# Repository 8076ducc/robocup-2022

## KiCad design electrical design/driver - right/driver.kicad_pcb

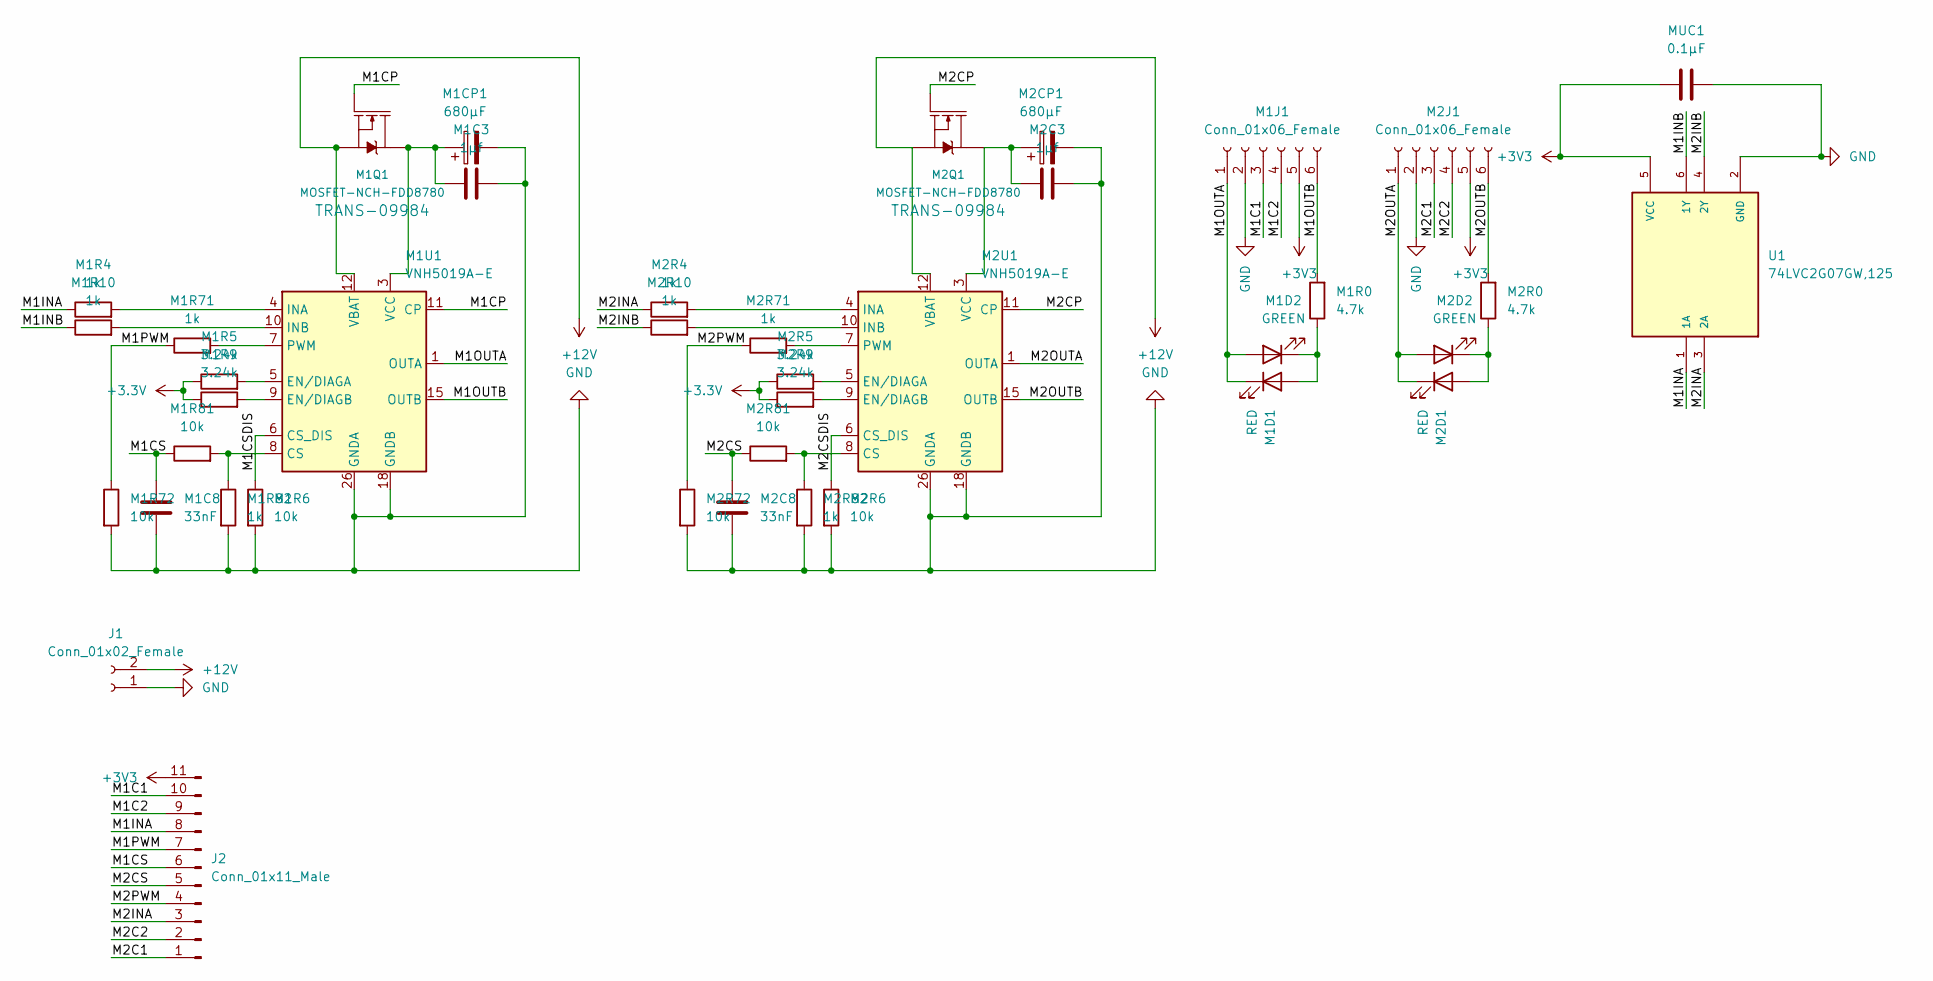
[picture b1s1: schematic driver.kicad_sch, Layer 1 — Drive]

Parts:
J1: Conn_01x02_Female; AMASS_XT30U-F_1x02_P5.0mm_Vertical
J2: Conn_01x11_Male; PinHeader_1x11_P2.54mm_Vertical
M1C3, M2C3: 1µf; C_0603_1608Metric
M1C8, M2C8: 33nF; C_0603_1608Metric
M1CP1, M2CP1: 680µF; CP_Radial_D8.0mm_P3.50mm
M1D1, M2D1: RED; LED-0603
M1D2, M2D2: GREEN; LED-0603
M1J1, M2J1: Conn_01x06_Female; JST_PH_B6B-PH-SM4-TB_1x06-1MP_P2.00mm_Vertical
M1Q1, M2Q1: MOSFET-NCH-FDD8780; DPAK
M1R0, M2R0: 4.7k; R_0603_1608Metric
M1R4, M1R10, M1R71, M1R82, M2R4, M2R10, M2R71, M2R82: 1k; R_0603_1608Metric
M1R5, M1R9, M2R5, M2R9: 3.24k; R_0603_1608Metric
M1R6, M1R72, M1R81, M2R6, M2R72, M2R81: 10k; R_0603_1608Metric
M1U1, M2U1: VNH5019A-E; ST_MultiPowerSO-30
MUC1: 0.1µF; C_0603_1608Metric
U1: 74LVC2G07GW,125; SOP65P210X110-6N

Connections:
+12V: J1.2, M1Q1.3 (S), M1U1.12 (VBAT), M2Q1.3 (S), M2U1.12 (VBAT)
/M1C1: J2.10, M1J1.3
/M1C2: J2.9, M1J1.4
/M1CP: M1Q1.1 (G), M1U1.11 (CP)
/M1CS: J2.6, M1C8.1, M1R81.1
/M1CSDIS: M1R6.1, M1U1.6 (CS_DIS)
/M1INA: J2.8, M1R4.1, U1.1 (1A)
/M1INB: M1R10.1, U1.6 (1Y)
/M1OUTA: M1D1.1 (K), M1D2.2 (A), M1J1.1, M1J1.MP, M1U1.1 (OUTA), M1U1.25 (OUTA), M1U1.30 (OUTA), M1U1.33 (OUTA)
/M1OUTB: M1J1.6, M1J1.MP, M1R0.2, M1U1.15 (OUTB), M1U1.16 (OUTB), M1U1.21 (OUTB), M1U1.32 (OUTB)
/M1PWM: J2.7, M1R71.1, M1R72.1
/M2C1: J2.1, M2J1.3
/M2C2: J2.2, M2J1.4
/M2CP: M2Q1.1 (G), M2U1.11 (CP)
/M2CS: J2.5, M2C8.1, M2R81.1
/M2CSDIS: M2R6.1, M2U1.6 (CS_DIS)
/M2INA: J2.3, M2R4.1, U1.3 (2A)
/M2INB: M2R10.1, U1.4 (2Y)
/M2OUTA: M2D1.1 (K), M2D2.2 (A), M2J1.1, M2U1.1 (OUTA), M2U1.25 (OUTA), M2U1.30 (OUTA), M2U1.33 (OUTA)
/M2OUTB: M2J1.6, M2R0.2, M2U1.15 (OUTB), M2U1.16 (OUTB), M2U1.21 (OUTB), M2U1.32 (OUTB)
/M2PWM: J2.4, M2R71.1, M2R72.1
GND: J1.1, M1C3.2, M1C8.2, M1CP1.2, M1J1.2, M1R6.2, M1R72.2, M1R82.2, M1U1.18 (GNDB), M1U1.19 (GNDB), M1U1.20 (GNDB), M1U1.26 (GNDA), M1U1.27 (GNDA), M1U1.28 (GNDA), M2C3.2, M2C8.2, M2CP1.2, M2J1.2, M2R6.2, M2R72.2, M2R82.2, M2U1.18 (GNDB), M2U1.19 (GNDB), M2U1.20 (GNDB), M2U1.26 (GNDA), M2U1.27 (GNDA), M2U1.28 (GNDA), MUC1.1, U1.2 (GND)
unnamed: M1C3.1, M1CP1.1, M1Q1.4 (D), M1U1.3 (VCC), M1U1.13 (VCC), M1U1.23 (VCC), M1U1.31 (VCC)
unnamed: M1D1.2 (A), M1D2.1 (K), M1R0.1
unnamed: M1R4.2, M1U1.4 (INA)
unnamed: M1R5.2, M1U1.5 (EN/DIAGA)
unnamed: M1R9.2, M1U1.9 (EN/DIAGB)
unnamed: M1R10.2, M1U1.10 (INB)
unnamed: M1R71.2, M1U1.7 (PWM)
unnamed: M1R81.2, M1R82.1, M1U1.8 (CS)
unnamed: M2C3.1, M2CP1.1, M2Q1.4 (D), M2U1.3 (VCC), M2U1.13 (VCC), M2U1.23 (VCC), M2U1.31 (VCC)
unnamed: M2D1.2 (A), M2D2.1 (K), M2R0.1
unnamed: M2R4.2, M2U1.4 (INA)
unnamed: M2R5.2, M2U1.5 (EN/DIAGA)
unnamed: M2R9.2, M2U1.9 (EN/DIAGB)
unnamed: M2R10.2, M2U1.10 (INB)
unnamed: M2R71.2, M2U1.7 (PWM)
unnamed: M2R81.2, M2R82.1, M2U1.8 (CS)

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
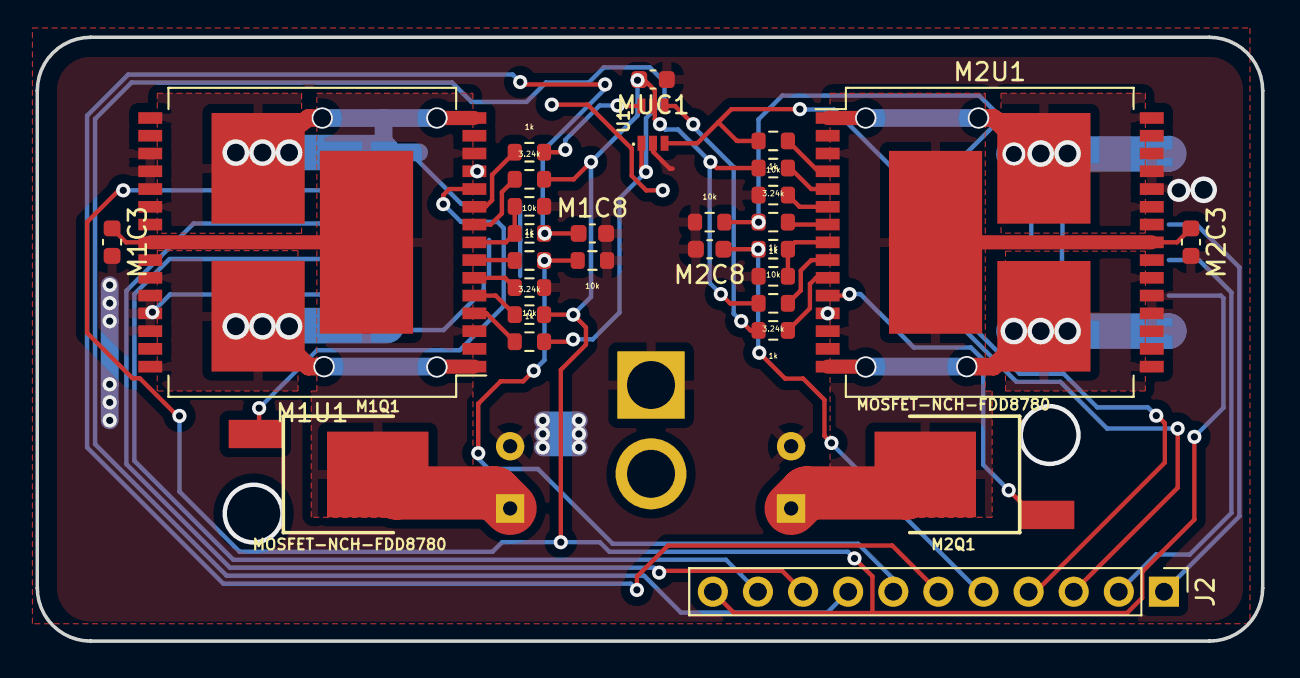
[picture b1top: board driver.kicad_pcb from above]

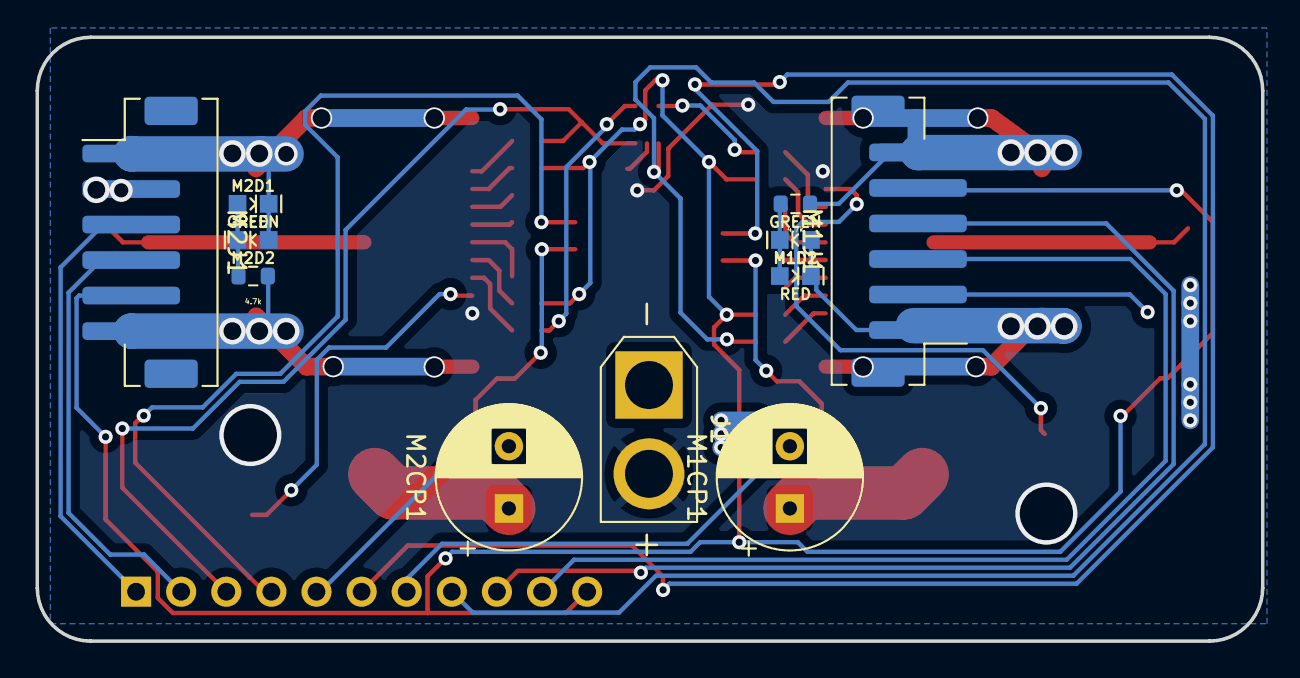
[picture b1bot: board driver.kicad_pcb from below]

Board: 2 copper layers, 69.0 x 34.0 mm, 40 parts (11 on the bottom side), 39 nets.

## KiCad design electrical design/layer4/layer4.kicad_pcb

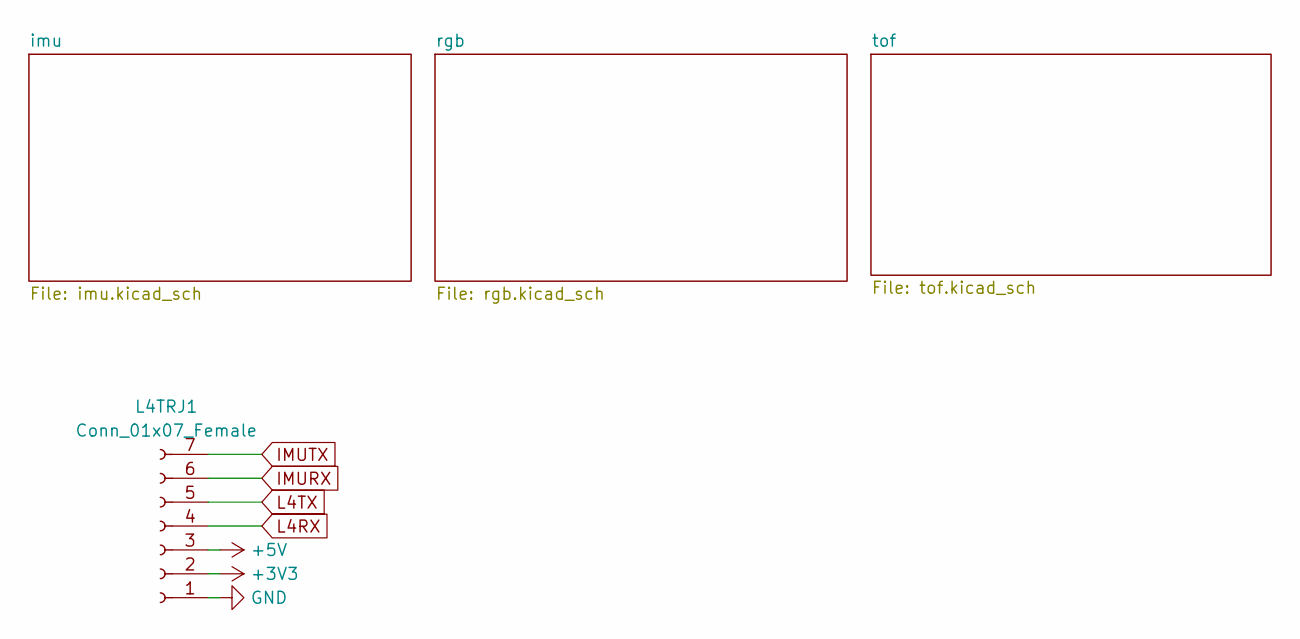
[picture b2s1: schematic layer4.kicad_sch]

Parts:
L4TRJ1: Conn_01x07_Female; JST_SH_BM07B-SRSS-TB_1x07-1MP_P1.00mm_Vertical

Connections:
+3V3: L4TRJ1.2; also elsewhere on the board
+5V: L4TRJ1.3; also elsewhere on the board
GND: L4TRJ1.1; also elsewhere on the board
IMURX: L4TRJ1.6; also elsewhere on the board
IMUTX: L4TRJ1.7; also elsewhere on the board
L4RX: L4TRJ1.4; also elsewhere on the board
L4TX: L4TRJ1.5; also elsewhere on the board

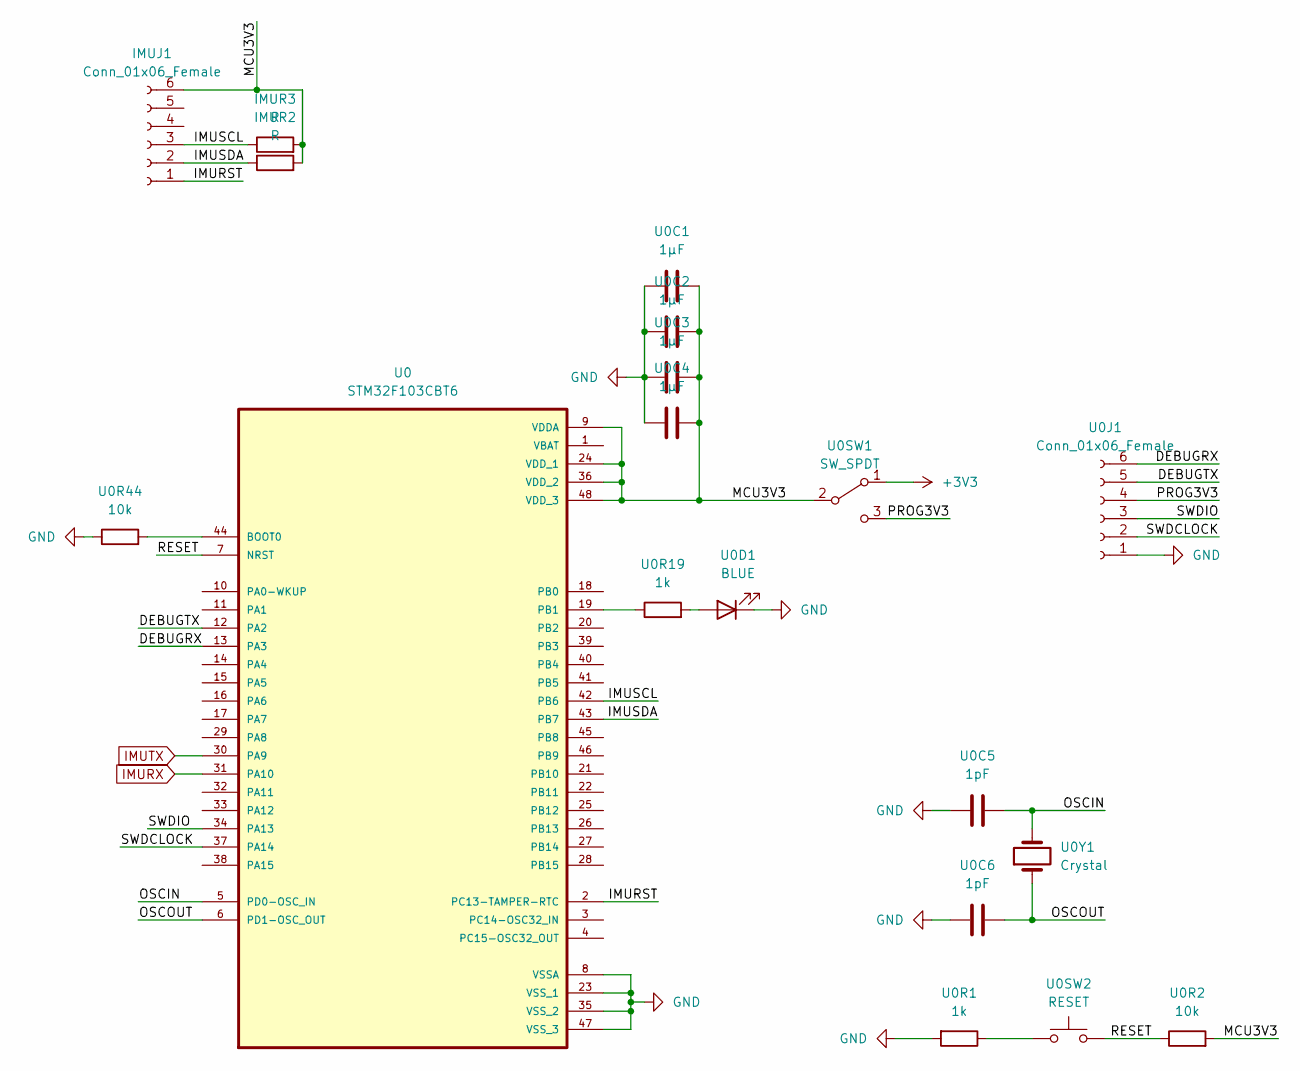
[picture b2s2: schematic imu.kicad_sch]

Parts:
IMUJ1: Conn_01x06_Female; 1X06_FEMALE_LOCK.010
IMUR2, IMUR3: R; 0603
U0: STM32F103CBT6; QFP50P900X900X160-48N; PARTREV 10
U0C1, U0C2, U0C3, U0C4: 1µF; 0603
U0C5, U0C6: 1pF; 0603
U0D1: BLUE; LED-0603
U0J1: Conn_01x06_Female; JST_SH_SM06B-SRSS-TB_1x06-1MP_P1.00mm_Horizontal
U0R1, U0R19: 1k; 0603
U0R2, U0R44: 10k; 0603
U0SW1: SW_SPDT; SWITCH_SPDT_PTH_11.6X4.0MM_LOCK
U0SW2: RESET; SW_Push_SPST_NO_Alps_SKRK
U0Y1: Crystal; CRYSTAL-SMD-5X3.2-2PAD

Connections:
+3V3: U0SW1.1 (A); also elsewhere on the board
/imu/DEBUGRX: U0.13 (PA3), U0J1.6
/imu/DEBUGTX: U0.12 (PA2), U0J1.5
/imu/IMURST: IMUJ1.1, U0.2 (PC13-TAMPER-RTC)
/imu/IMUSCL: IMUJ1.3, IMUR3.1, U0.42 (PB6)
/imu/IMUSDA: IMUJ1.2, IMUR2.1, U0.43 (PB7)
/imu/MCU3V3: IMUJ1.6, IMUR2.2, IMUR3.2, U0.9 (VDDA), U0.24 (VDD_1), U0.36 (VDD_2), U0.48 (VDD_3), U0C1.2, U0C2.2, U0C3.2, U0C4.2, U0R2.2, U0SW1.2 (B)
/imu/OSCIN: U0.5 (PD0-OSC_IN), U0C5.2, U0Y1.2
/imu/OSCOUT: U0.6 (PD1-OSC_OUT), U0C6.2, U0Y1.1
/imu/PROG3V3: U0J1.4, U0SW1.3 (C)
/imu/RESET: U0.7 (NRST), U0R2.1, U0SW2.2
/imu/SWDCLOCK: U0.37 (PA14), U0J1.2
/imu/SWDIO: U0.34 (PA13), U0J1.3
GND: U0.8 (VSSA), U0.23 (VSS_1), U0.35 (VSS_2), U0.47 (VSS_3), U0C1.1, U0C2.1, U0C3.1, U0C4.1, U0C5.1, U0C6.1, U0D1.1 (K), U0J1.1, U0R1.2, U0R44.1; also elsewhere on the board
IMURX: U0.31 (PA10); also elsewhere on the board
IMUTX: U0.30 (PA9); also elsewhere on the board
unnamed: U0.19 (PB1), U0R19.1
unnamed: U0.44 (BOOT0), U0R44.2
unnamed: U0D1.2 (A), U0R19.2
unnamed: U0R1.1, U0SW2.1

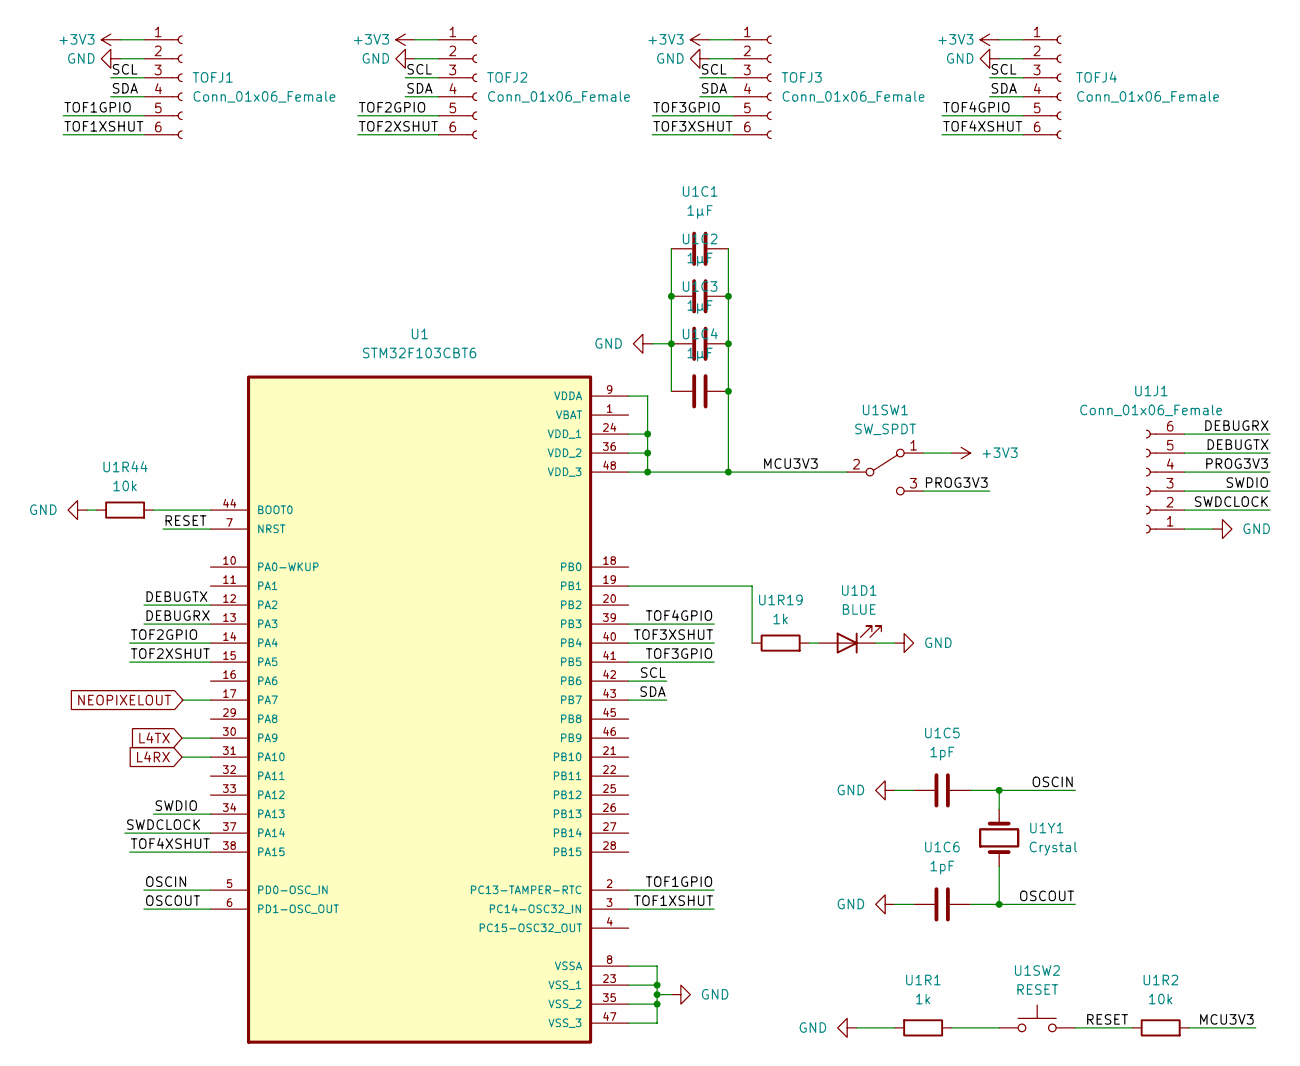
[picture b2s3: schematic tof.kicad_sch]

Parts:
TOFJ1, TOFJ2, TOFJ3, TOFJ4: Conn_01x06_Female; 1X06_FEMALE_LOCK.010
U1: STM32F103CBT6; QFP50P900X900X160-48N; PARTREV 10
U1C1, U1C2, U1C3, U1C4: 1µF; 0603
U1C5, U1C6: 1pF; 0603
U1D1: BLUE; LED-0603
U1J1: Conn_01x06_Female; JST_SH_SM06B-SRSS-TB_1x06-1MP_P1.00mm_Horizontal
U1R1, U1R19: 1k; 0603
U1R2, U1R44: 10k; 0603
U1SW1: SW_SPDT; SWITCH_SPDT_PTH_11.6X4.0MM_LOCK
U1SW2: RESET; SW_Push_SPST_NO_Alps_SKRK
U1Y1: Crystal; CRYSTAL-SMD-5X3.2-2PAD

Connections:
+3V3: TOFJ1.1, TOFJ2.1, TOFJ3.1, TOFJ4.1, U1SW1.1 (A); also elsewhere on the board
/tof/DEBUGRX: U1.13 (PA3), U1J1.6
/tof/DEBUGTX: U1.12 (PA2), U1J1.5
/tof/MCU3V3: U1.9 (VDDA), U1.24 (VDD_1), U1.36 (VDD_2), U1.48 (VDD_3), U1C1.2, U1C2.2, U1C3.2, U1C4.2, U1R2.2, U1SW1.2 (B)
/tof/OSCIN: U1.5 (PD0-OSC_IN), U1C5.2, U1Y1.2
/tof/OSCOUT: U1.6 (PD1-OSC_OUT), U1C6.2, U1Y1.1
/tof/PROG3V3: U1J1.4, U1SW1.3 (C)
/tof/RESET: U1.7 (NRST), U1R2.1, U1SW2.2
/tof/SCL: TOFJ1.3, TOFJ2.3, TOFJ3.3, TOFJ4.3, U1.42 (PB6)
/tof/SDA: TOFJ1.4, TOFJ2.4, TOFJ3.4, TOFJ4.4, U1.43 (PB7)
/tof/SWDCLOCK: U1.37 (PA14), U1J1.2
/tof/SWDIO: U1.34 (PA13), U1J1.3
/tof/TOF1GPIO: TOFJ1.5, U1.2 (PC13-TAMPER-RTC)
/tof/TOF1XSHUT: TOFJ1.6, U1.3 (PC14-OSC32_IN)
/tof/TOF2GPIO: TOFJ2.5, U1.14 (PA4)
/tof/TOF2XSHUT: TOFJ2.6, U1.15 (PA5)
/tof/TOF3GPIO: TOFJ3.5, U1.41 (PB5)
/tof/TOF3XSHUT: TOFJ3.6, U1.40 (PB4)
/tof/TOF4GPIO: TOFJ4.5, U1.39 (PB3)
/tof/TOF4XSHUT: TOFJ4.6, U1.38 (PA15)
GND: TOFJ1.2, TOFJ2.2, TOFJ3.2, TOFJ4.2, U1.8 (VSSA), U1.23 (VSS_1), U1.35 (VSS_2), U1.47 (VSS_3), U1C1.1, U1C2.1, U1C3.1, U1C4.1, U1C5.1, U1C6.1, U1D1.1 (K), U1J1.1, U1R1.2, U1R44.1; also elsewhere on the board
L4RX: U1.31 (PA10); also elsewhere on the board
L4TX: U1.30 (PA9); also elsewhere on the board
NEOPIXELOUT: U1.17 (PA7); also elsewhere on the board
unnamed: U1.19 (PB1), U1R19.1
unnamed: U1.44 (BOOT0), U1R44.2
unnamed: U1D1.2 (A), U1R19.2
unnamed: U1R1.1, U1SW2.1

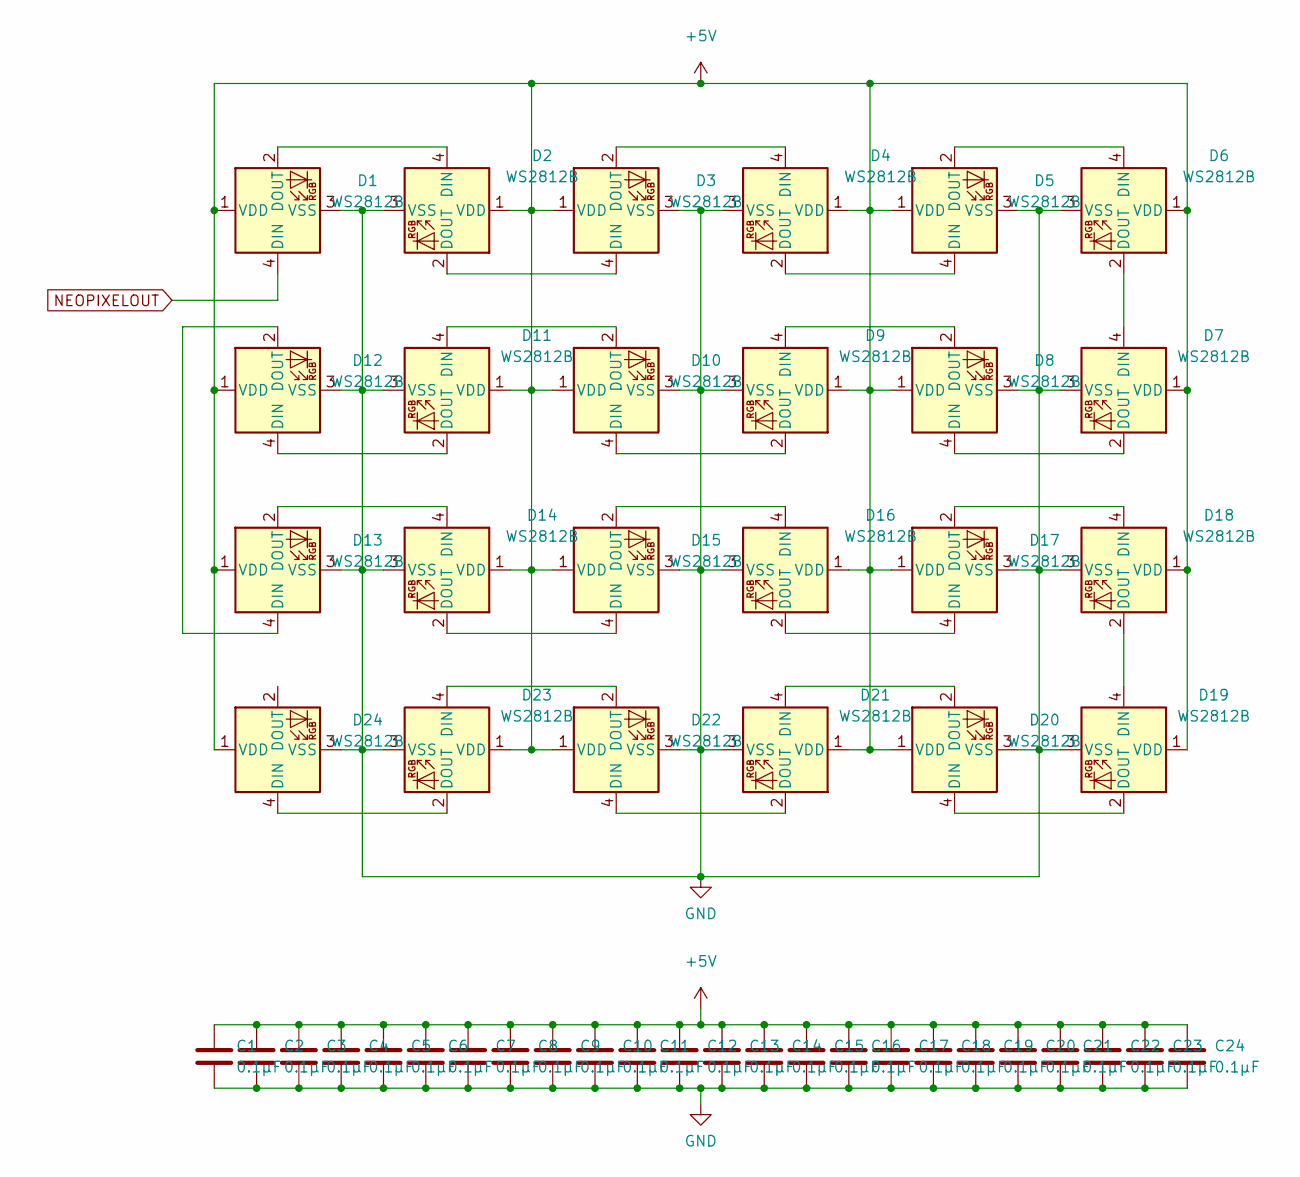
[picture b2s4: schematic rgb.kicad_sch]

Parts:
C1, C2, C3, C4, C5, C6, C7, C8, C9, C10, C11, C12, C13, C14, C15, C16, C17, C18, C19, C20, C21, C22, C23, C24: 0.1µF; 0603
D1, D2, D3, D4, D5, D6, D7, D8, D9, D10, D11, D12, D13, D14, D15, D16, D17, D18, D19, D20, D21, D22, D23, D24: WS2812B

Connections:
+5V: C1.1, C2.1, C3.1, C4.1, C5.1, C6.1, C7.1, C8.1, C9.1, C10.1, C11.1, C12.1, C13.1, C14.1, C15.1, C16.1, C17.1, C18.1, C19.1, C20.1, C21.1, C22.1, C23.1, C24.1, D1.1 (VDD), D2.1 (VDD), D3.1 (VDD), D4.1 (VDD), D5.1 (VDD), D6.1 (VDD), D7.1 (VDD), D8.1 (VDD), D9.1 (VDD), D10.1 (VDD), D11.1 (VDD), D12.1 (VDD), D13.1 (VDD), D14.1 (VDD), D15.1 (VDD), D16.1 (VDD), D17.1 (VDD), D18.1 (VDD), D19.1 (VDD), D20.1 (VDD), D21.1 (VDD), D22.1 (VDD), D23.1 (VDD), D24.1 (VDD); also elsewhere on the board
GND: C1.2, C2.2, C3.2, C4.2, C5.2, C6.2, C7.2, C8.2, C9.2, C10.2, C11.2, C12.2, C13.2, C14.2, C15.2, C16.2, C17.2, C18.2, C19.2, C20.2, C21.2, C22.2, C23.2, C24.2, D1.3 (VSS), D2.3 (VSS), D3.3 (VSS), D4.3 (VSS), D5.3 (VSS), D6.3 (VSS), D7.3 (VSS), D8.3 (VSS), D9.3 (VSS), D10.3 (VSS), D11.3 (VSS), D12.3 (VSS), D13.3 (VSS), D14.3 (VSS), D15.3 (VSS), D16.3 (VSS), D17.3 (VSS), D18.3 (VSS), D19.3 (VSS), D20.3 (VSS), D21.3 (VSS), D22.3 (VSS), D23.3 (VSS), D24.3 (VSS); also elsewhere on the board
NEOPIXELOUT: D1.4 (DIN); also elsewhere on the board
unnamed: D1.2 (DOUT), D2.4 (DIN)
unnamed: D2.2 (DOUT), D3.4 (DIN)
unnamed: D3.2 (DOUT), D4.4 (DIN)
unnamed: D4.2 (DOUT), D5.4 (DIN)
unnamed: D5.2 (DOUT), D6.4 (DIN)
unnamed: D6.2 (DOUT), D7.4 (DIN)
unnamed: D7.2 (DOUT), D8.4 (DIN)
unnamed: D8.2 (DOUT), D9.4 (DIN)
unnamed: D10.2 (DOUT), D11.4 (DIN)
unnamed: D9.2 (DOUT), D10.4 (DIN)
unnamed: D11.2 (DOUT), D12.4 (DIN)
unnamed: D12.2 (DOUT), D13.4 (DIN)
unnamed: D13.2 (DOUT), D14.4 (DIN)
unnamed: D14.2 (DOUT), D15.4 (DIN)
unnamed: D15.2 (DOUT), D16.4 (DIN)
unnamed: D16.2 (DOUT), D17.4 (DIN)
unnamed: D17.2 (DOUT), D18.4 (DIN)
unnamed: D18.2 (DOUT), D19.4 (DIN)
unnamed: D19.2 (DOUT), D20.4 (DIN)
unnamed: D20.2 (DOUT), D21.4 (DIN)
unnamed: D21.2 (DOUT), D22.4 (DIN)
unnamed: D22.2 (DOUT), D23.4 (DIN)
unnamed: D23.2 (DOUT), D24.4 (DIN)

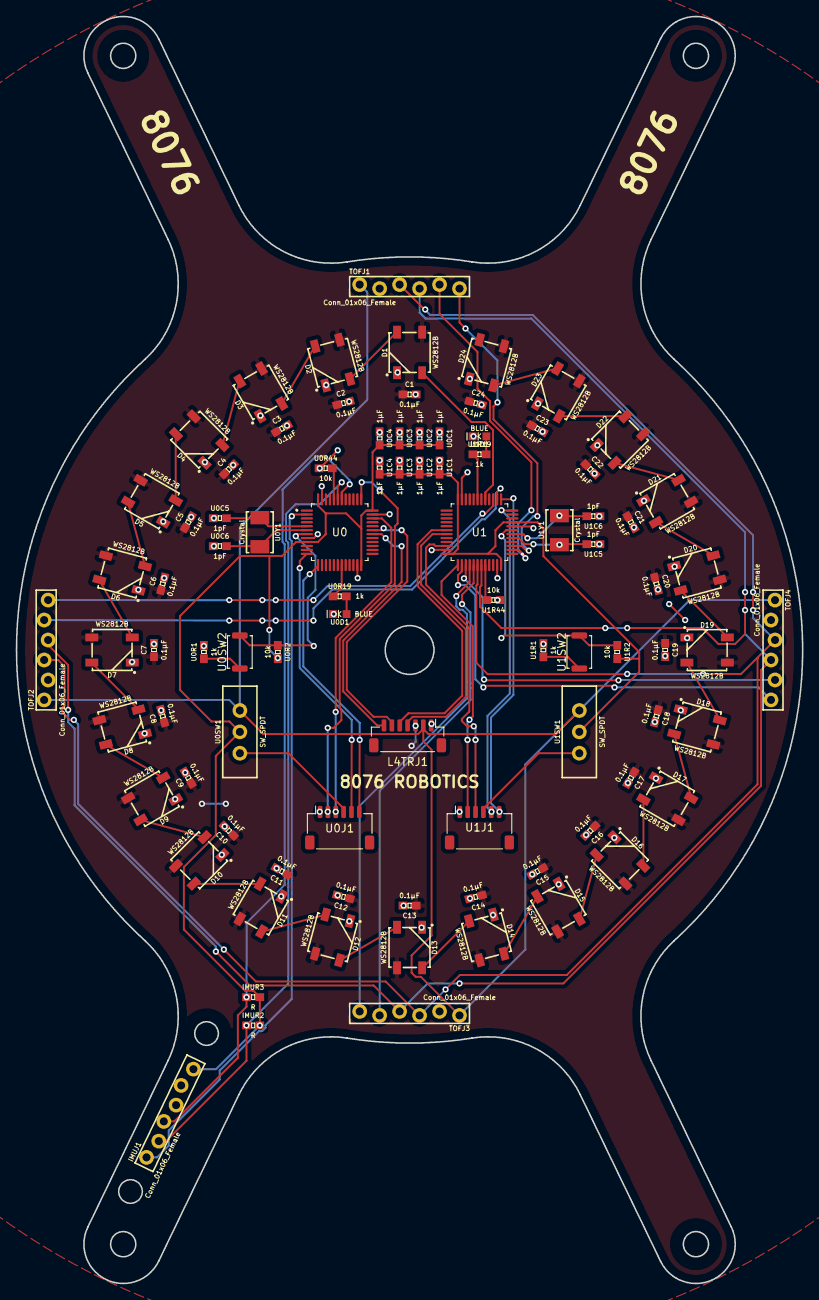
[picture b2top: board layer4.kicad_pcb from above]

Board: 2 copper layers, 100.0 x 161.2 mm, 88 parts (0 on the bottom side), 70 nets.

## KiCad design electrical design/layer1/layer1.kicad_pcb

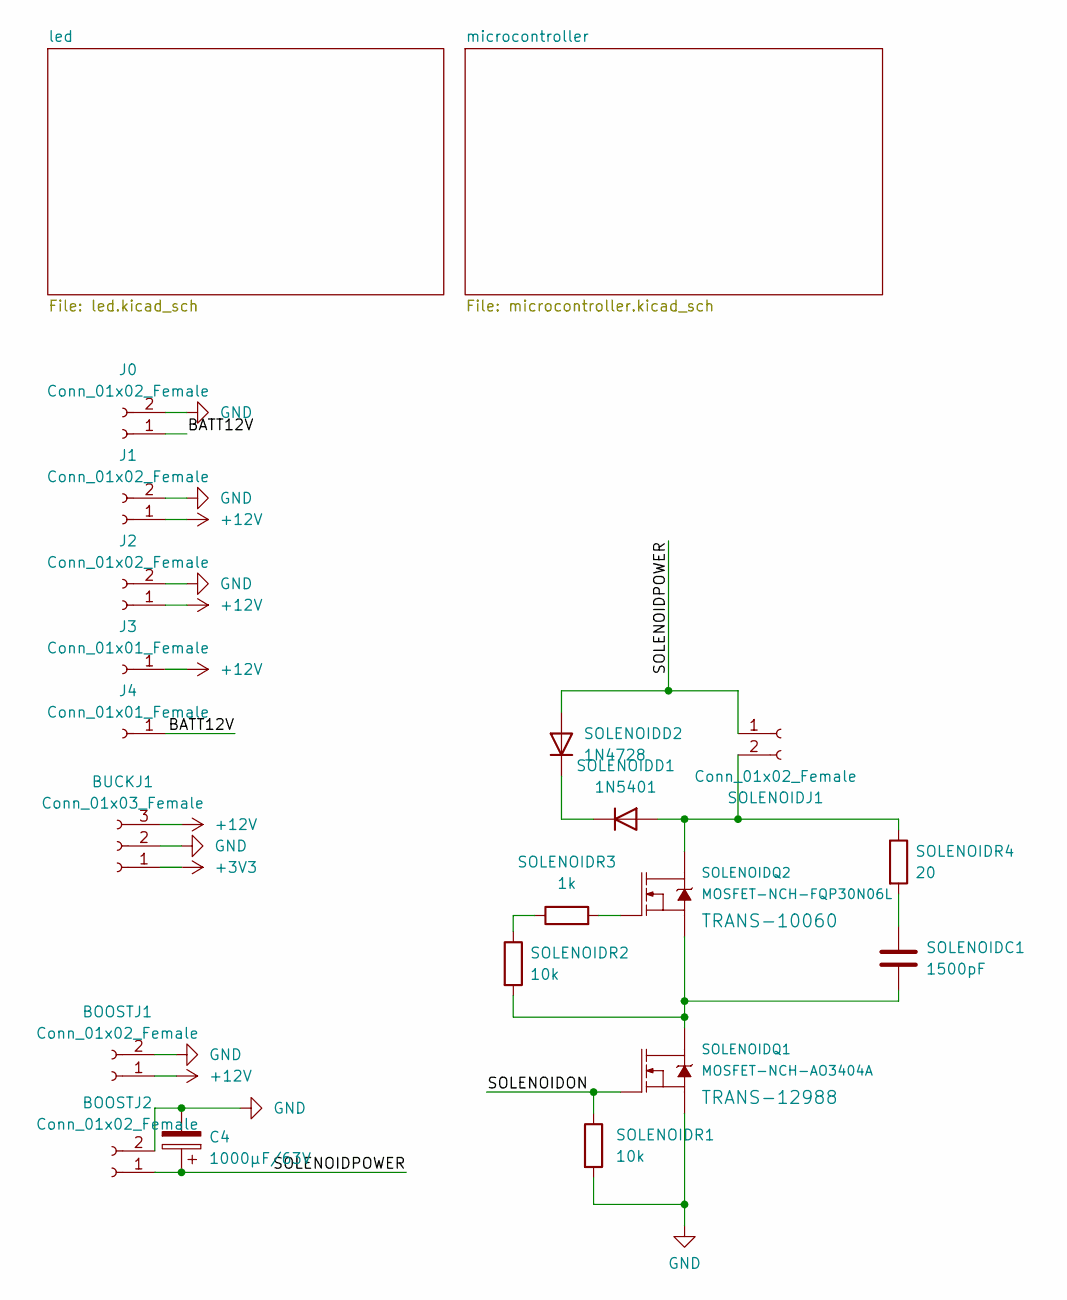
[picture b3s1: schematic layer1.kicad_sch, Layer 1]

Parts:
BOOSTJ1, BOOSTJ2: Conn_01x02_Female; AMASS_XT30U-F_1x02_P5.0mm_Vertical
BUCKJ1: Conn_01x03_Female; 1X03_LOCK
C4: 1000µF/63V; CP_Radial_D16.0mm_P7.50mm
J0, J1, J2: Conn_01x02_Female; AMASS_XT60-F_1x02_P7.20mm_Vertical
J3, J4: Conn_01x01_Female; 14AWG
SOLENOIDC1: 1500pF; 0603
SOLENOIDD1: 1N5401; D_DO-27_P15.24mm_Horizontal
SOLENOIDD2: 1N4728; D_DO-41_SOD81_P10.16mm_Horizontal
SOLENOIDJ1: Conn_01x02_Female; AMASS_XT30U-F_1x02_P5.0mm_Vertical
SOLENOIDQ1: MOSFET-NCH-AO3404A; SOT23-3
SOLENOIDQ2: MOSFET-NCH-FQP30N06L; TO-220-3_Vertical
SOLENOIDR1, SOLENOIDR2: 10k; 0603
SOLENOIDR3: 1k; 0603
SOLENOIDR4: 20; 0603

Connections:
+3V3: BUCKJ1.1; also elsewhere on the board
+12V: BOOSTJ1.1, BUCKJ1.3, J1.1, J2.1, J3.1
/BATT12V: J0.1, J4.1
/SOLENOIDON: SOLENOIDQ1.1 (G), SOLENOIDR1.1
/SOLENOIDPOWER: BOOSTJ2.1, C4.1, SOLENOIDD2.2 (A), SOLENOIDJ1.1
GND: BOOSTJ1.2, BOOSTJ2.2, BUCKJ1.2, C4.2, J0.2, J1.2, J2.2, SOLENOIDQ1.2 (S), SOLENOIDR1.2; also elsewhere on the board
unnamed: SOLENOIDC1.1, SOLENOIDR4.2
unnamed: SOLENOIDC1.2, SOLENOIDQ1.3 (D), SOLENOIDQ2.3 (S), SOLENOIDR2.2
unnamed: SOLENOIDD1.1 (K), SOLENOIDD2.1 (K)
unnamed: SOLENOIDD1.2 (A), SOLENOIDJ1.2, SOLENOIDQ2.2 (D), SOLENOIDR4.1
unnamed: SOLENOIDQ2.1 (G), SOLENOIDR3.2
unnamed: SOLENOIDR2.1, SOLENOIDR3.1

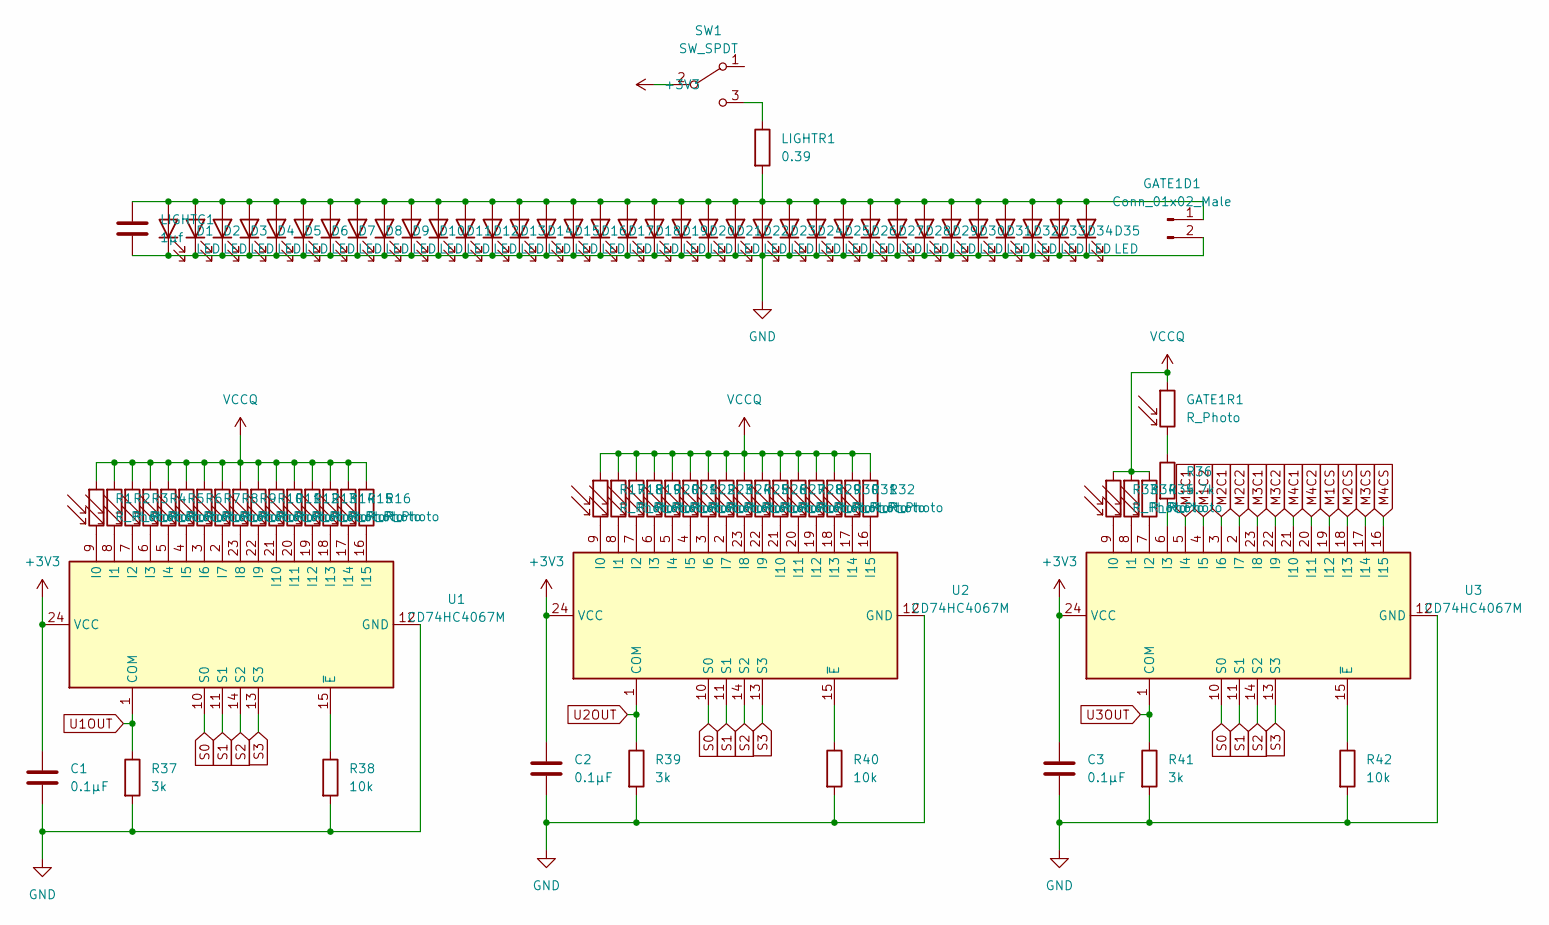
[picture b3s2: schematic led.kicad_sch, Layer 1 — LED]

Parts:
C1, C2, C3: 0.1µF; 0603
D1, D2, D3, D4, D5, D6, D7, D8, D9, D10, D11, D12, D13, D14, D15, D16, D17, D18, D19, D20, D21, D22, D23, D24, D25, D26, D27, D28, D29, D30, D31, D32, D33, D34, D35: LED; LED_OF-SMD3528WC
GATE1D1: Conn_01x02_Male; 1X02_LOCK
GATE1R1: R_Photo; 1X02_LOCK
LIGHTC1: 1µf; 0603
LIGHTR1: 0.39; 0603
R1, R2, R3, R4, R5, R6, R7, R8, R9, R10, R11, R12, R13, R14, R15, R16, R17, R18, R19, R20, R21, R22, R23, R24, R25, R26, R27, R28, R29, R30, R31, R32, R33, R34, R35: R_Photo; XDCR_ALS-PT19-315C_L177_TR8
R36: 4.7k; 0603
R37, R39, R41: 3k; 0603
R38, R40, R42: 10k; 0603
SW1: SW_SPDT; SWITCH_SPDT_PTH_11.6X4.0MM_LOCK
U1, U2, U3: CD74HC4067M; SOIC-24W_7.5x15.4mm_P1.27mm

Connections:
+3V3: C1.1, C2.1, C3.1, SW1.2 (B), U1.24 (VCC), U2.24 (VCC), U3.24 (VCC); also elsewhere on the board
GND: C1.2, C2.2, C3.2, D1.1 (K), D2.1 (K), D3.1 (K), D4.1 (K), D5.1 (K), D6.1 (K), D7.1 (K), D8.1 (K), D9.1 (K), D10.1 (K), D11.1 (K), D12.1 (K), D13.1 (K), D14.1 (K), D15.1 (K), D16.1 (K), D17.1 (K), D18.1 (K), D19.1 (K), D20.1 (K), D21.1 (K), D22.1 (K), D23.1 (K), D24.1 (K), D25.1 (K), D26.1 (K), D27.1 (K), D28.1 (K), D29.1 (K), D30.1 (K), D31.1 (K), D32.1 (K), D33.1 (K), D34.1 (K), D35.1 (K), GATE1D1.2, LIGHTC1.2, R37.2, R38.2, R39.2, R40.2, R41.2, R42.2, U1.12 (GND), U2.12 (GND), U3.12 (GND); also elsewhere on the board
M1C1: U3.5 (I4); also elsewhere on the board
M1C2: U3.4 (I5); also elsewhere on the board
M1CS: U3.19 (I12); also elsewhere on the board
M2C1: U3.3 (I6); also elsewhere on the board
M2C2: U3.2 (I7); also elsewhere on the board
M2CS: U3.18 (I13); also elsewhere on the board
M3C1: U3.23 (I8); also elsewhere on the board
M3C2: U3.22 (I9); also elsewhere on the board
M3CS: U3.17 (I14); also elsewhere on the board
M4C1: U3.21 (I10); also elsewhere on the board
M4C2: U3.20 (I11); also elsewhere on the board
M4CS: U3.16 (I15); also elsewhere on the board
unnamed: D1.2 (A), D2.2 (A), D3.2 (A), D4.2 (A), D5.2 (A), D6.2 (A), D7.2 (A), D8.2 (A), D9.2 (A), D10.2 (A), D11.2 (A), D12.2 (A), D13.2 (A), D14.2 (A), D15.2 (A), D16.2 (A), D17.2 (A), D18.2 (A), D19.2 (A), D20.2 (A), D21.2 (A), D22.2 (A), D23.2 (A), D24.2 (A), D25.2 (A), D26.2 (A), D27.2 (A), D28.2 (A), D29.2 (A), D30.2 (A), D31.2 (A), D32.2 (A), D33.2 (A), D34.2 (A), D35.2 (A), GATE1D1.1, LIGHTC1.1, LIGHTR1.2
unnamed: GATE1R1.2, R36.1
unnamed: LIGHTR1.1, SW1.3 (C)
unnamed: R1.2, U1.9 (I0)
unnamed: R2.2, U1.8 (I1)
unnamed: R3.2, U1.7 (I2)
unnamed: R4.2, U1.6 (I3)
unnamed: R5.2, U1.5 (I4)
unnamed: R6.2, U1.4 (I5)
unnamed: R7.2, U1.3 (I6)
unnamed: R8.2, U1.2 (I7)
unnamed: R9.2, U1.23 (I8)
unnamed: R10.2, U1.22 (I9)
unnamed: R11.2, U1.21 (I10)
unnamed: R12.2, U1.20 (I11)
unnamed: R13.2, U1.19 (I12)
unnamed: R14.2, U1.18 (I13)
unnamed: R15.2, U1.17 (I14)
unnamed: R16.2, U1.16 (I15)
unnamed: R17.2, U2.9 (I0)
unnamed: R18.2, U2.8 (I1)
unnamed: R19.2, U2.7 (I2)
unnamed: R20.2, U2.6 (I3)
unnamed: R21.2, U2.5 (I4)
unnamed: R22.2, U2.4 (I5)
unnamed: R23.2, U2.3 (I6)
unnamed: R24.2, U2.2 (I7)
unnamed: R25.2, U2.23 (I8)
unnamed: R26.2, U2.22 (I9)
unnamed: R27.2, U2.21 (I10)
unnamed: R28.2, U2.20 (I11)
unnamed: R29.2, U2.19 (I12)
unnamed: R30.2, U2.18 (I13)
unnamed: R31.2, U2.17 (I14)
unnamed: R32.2, U2.16 (I15)
unnamed: R33.2, U3.9 (I0)
unnamed: R34.2, U3.8 (I1)
unnamed: R35.2, U3.7 (I2)
unnamed: R36.2, U3.6 (I3)
unnamed: R38.1, U1.15 (~E)
unnamed: R40.1, U2.15 (~E)
unnamed: R42.1, U3.15 (~E)
S0: U1.10 (S0), U2.10 (S0), U3.10 (S0); also elsewhere on the board
S1: U1.11 (S1), U2.11 (S1), U3.11 (S1); also elsewhere on the board
S2: U1.14 (S2), U2.14 (S2), U3.14 (S2); also elsewhere on the board
S3: U1.13 (S3), U2.13 (S3), U3.13 (S3); also elsewhere on the board
U1OUT: R37.1, U1.1 (COM); also elsewhere on the board
U2OUT: R39.1, U2.1 (COM); also elsewhere on the board
U3OUT: R41.1, U3.1 (COM); also elsewhere on the board
VCCQ: GATE1R1.1, R1.1, R2.1, R3.1, R4.1, R5.1, R6.1, R7.1, R8.1, R9.1, R10.1, R11.1, R12.1, R13.1, R14.1, R15.1, R16.1, R17.1, R18.1, R19.1, R20.1, R21.1, R22.1, R23.1, R24.1, R25.1, R26.1, R27.1, R28.1, R29.1, R30.1, R31.1, R32.1, R33.1, R34.1, R35.1; also elsewhere on the board
